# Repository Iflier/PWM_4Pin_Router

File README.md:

# PWM_4Pin_Router
这是一个用于控制 `4 Pin` 风扇的扩展板。
板载 4路 4Pin风扇接口以及用于控制占空比的插针。
## 这是板子的正面

## 这是板子的背面

## 这是已经焊好的实物图

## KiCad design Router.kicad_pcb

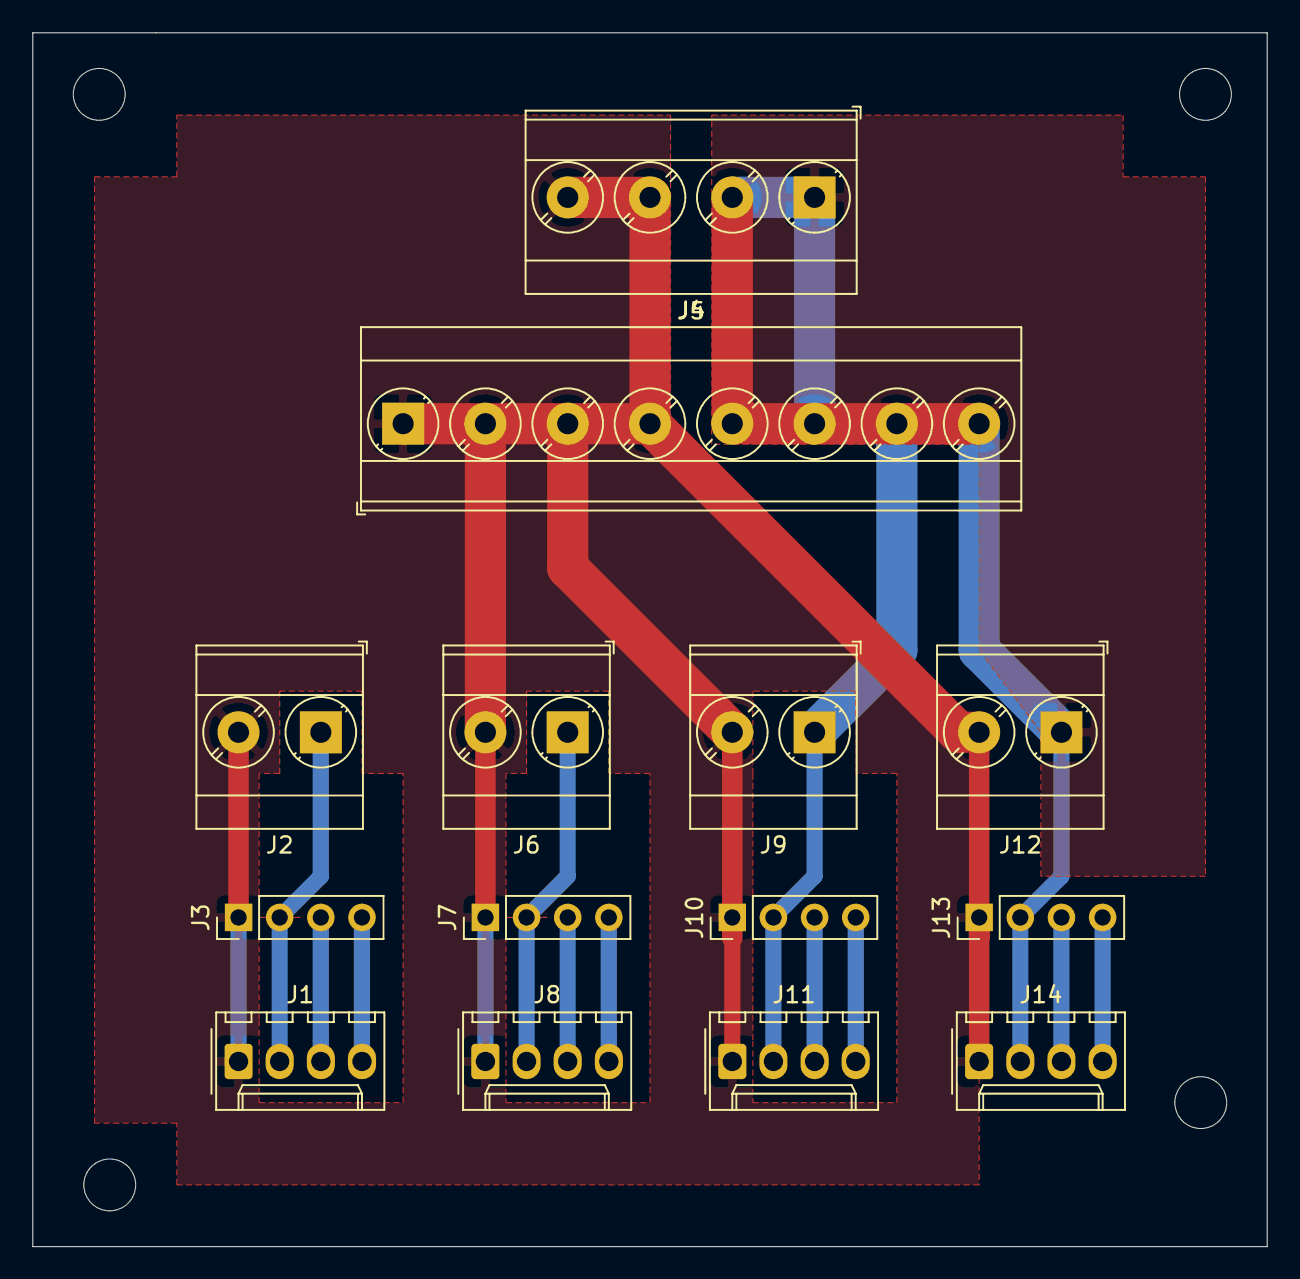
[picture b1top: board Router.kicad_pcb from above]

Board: 2 copper layers, 76.2 x 74.9 mm, 14 parts (0 on the bottom side), 10 nets.

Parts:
J1, J8, J11, J14: Screw_Terminal_01x04; Molex_KK-254_AE-6410-04A_1x04_P2.54mm_Vertical
J2, J6, J9, J12: Screw_Terminal_01x02; TerminalBlock_Phoenix_MKDS-3-2-5.08_1x02_P5.08mm_Horizontal
J3, J7, J10, J13: Screw_Terminal_01x04; PinHeader_1x04_P2.54mm_Vertical
J4: Screw_Terminal_01x04; TerminalBlock_Phoenix_MKDS-3-4-5.08_1x04_P5.08mm_Horizontal
J5: Screw_Terminal_01x08; TerminalBlock_Phoenix_MKDS-3-8-5.08_1x08_P5.08mm_Horizontal

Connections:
unnamed: J1.1, J2.2, J3.1, J4.3, J4.4, J5.1, J5.2, J5.3, J5.4, J6.2, J7.1, J8.1, J9.2, J10.1, J11.1, J12.2, J13.1, J14.1
unnamed: J1.2, J2.1, J3.2, J4.1, J4.2, J5.5, J5.6, J5.7, J5.8, J6.1, J7.2, J8.2, J9.1, J10.2, J11.2, J12.1, J13.2, J14.2
unnamed: J1.3, J3.3
unnamed: J1.4, J3.4
unnamed: J7.3, J8.3
unnamed: J7.4, J8.4
unnamed: J10.3, J11.3
unnamed: J10.4, J11.4
unnamed: J13.3, J14.3
unnamed: J13.4, J14.4

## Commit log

2020-10-31 上传实物图片
2020-10-31 添加图片链接
